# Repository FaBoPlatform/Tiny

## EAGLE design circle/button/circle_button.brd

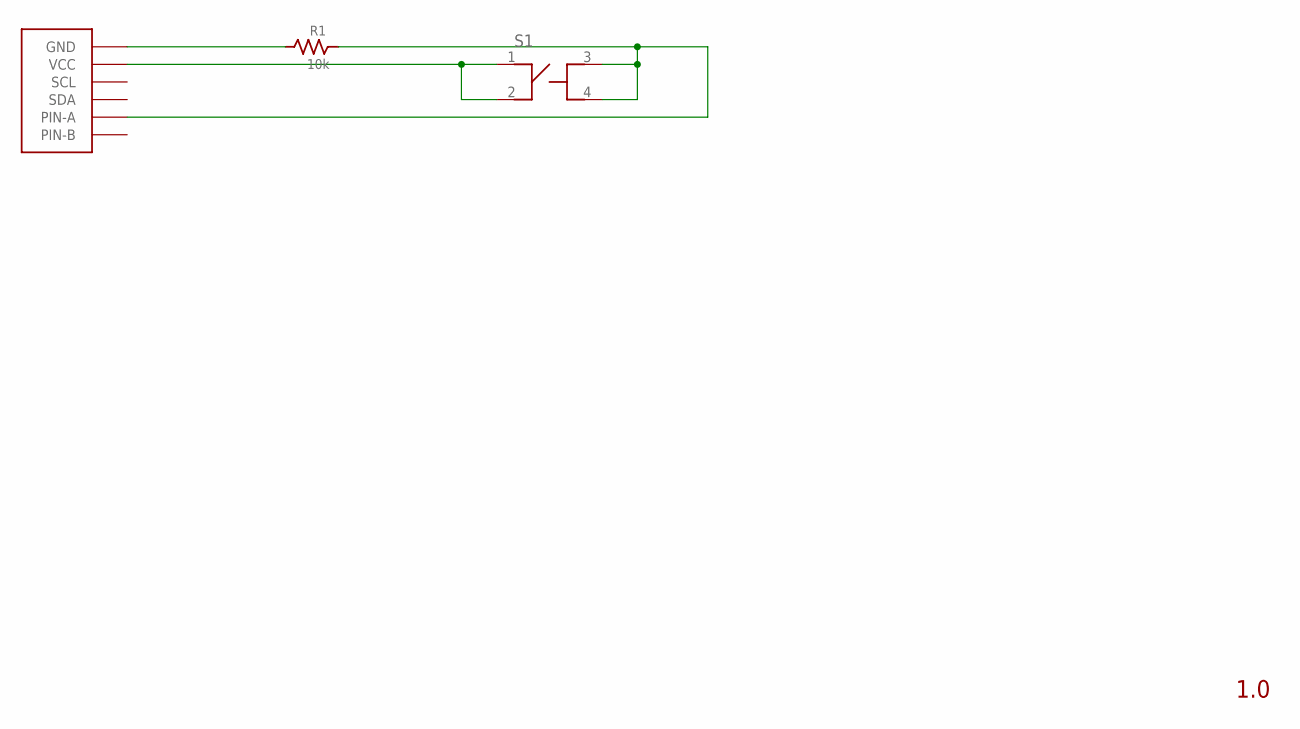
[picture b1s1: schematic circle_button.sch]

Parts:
R1: 10k; 0402
S1: SWITCH-LS6J2M-T
U$2: FABO-NANO

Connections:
GND: R1.P$1 (1), U$2.GND
unnamed: S1.1, S1.2, U$2.VCC
unnamed: R1.P$2 (2), S1.3, S1.4, U$2.2 (PIN-A)

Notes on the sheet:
1.0

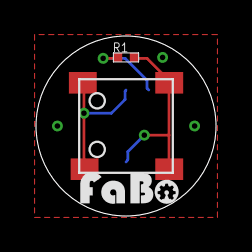
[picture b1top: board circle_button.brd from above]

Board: 2 copper layers, 10.0 x 10.0 mm, 4 parts (0 on the bottom side), 3 nets.

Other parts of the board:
U$1: LOGO_FABO_S

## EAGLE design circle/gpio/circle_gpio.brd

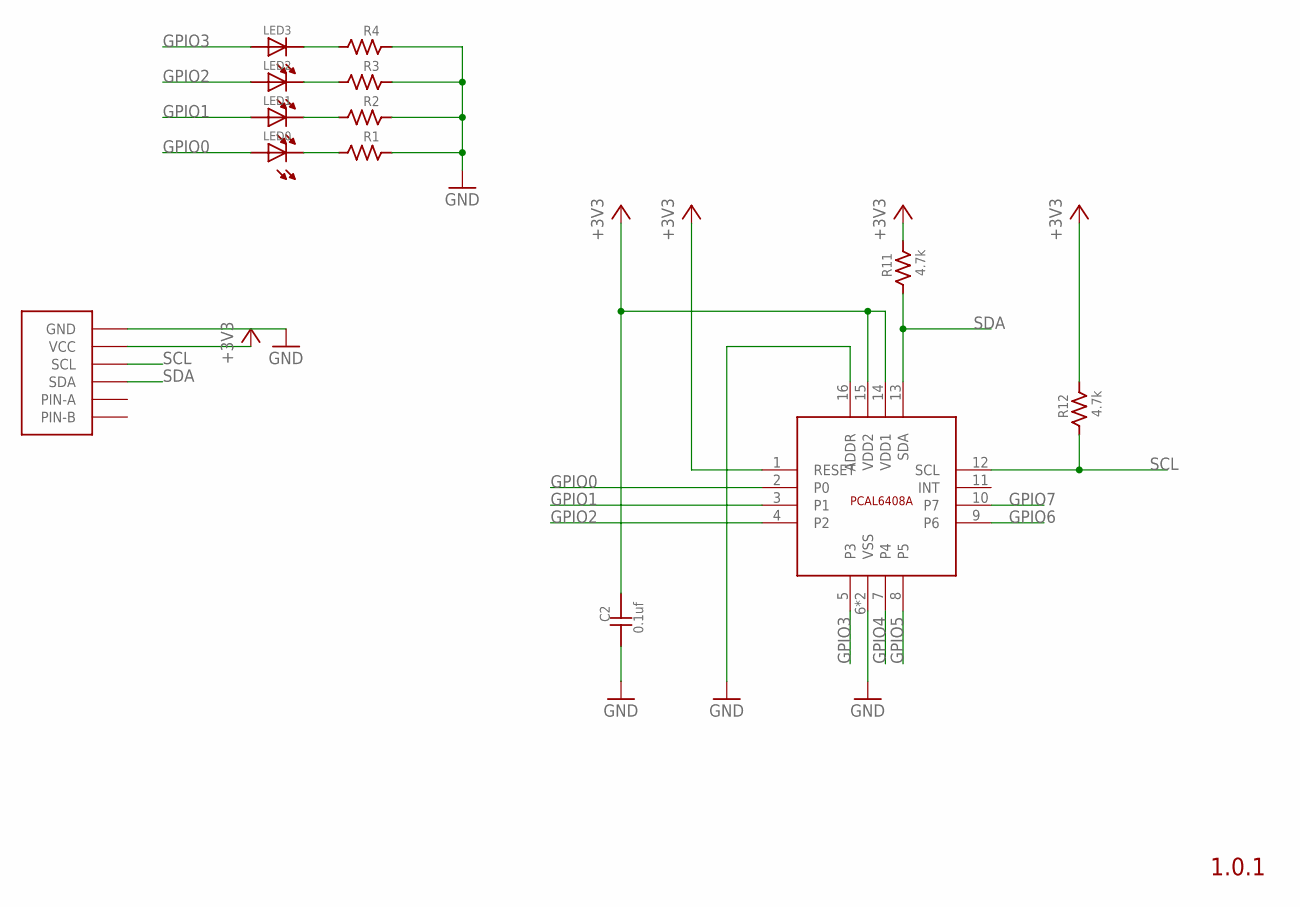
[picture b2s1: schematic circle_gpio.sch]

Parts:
C2: 0.1uf; 0402
LED0, LED1, LED2, LED3: LED0402; 0402
R1, R2, R3, R4: RESISTOR-0402; 0402
R11, R12: 4.7k; 0402
U$3: FABO-NANO
U$5: NX-PCAL6408A; NXP-PCAL6408A

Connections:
111: C2.P$1 (1), R1.P$2 (2), R2.P$2 (2), R3.P$2 (2), R4.P$2 (2), U$3.GND, U$5.6 (VSS), U$5.16 (ADDR), U$5.17 (VSS)
+3V3: C2.P$2 (2), R11.P$2 (2), R12.P$2 (2), U$3.VCC, U$5.1 (RESET), U$5.14 (VDD1), U$5.15 (VDD2)
GPIO0: LED0.ANODE, U$5.2 (P0)
GPIO1: LED1.ANODE, U$5.3 (P1)
GPIO2: LED2.ANODE, U$5.4 (P2)
GPIO3: LED3.ANODE, U$5.5 (P3)
GPIO4: U$5.7 (P4)
GPIO5: U$5.8 (P5)
GPIO6: U$5.9 (P6)
GPIO7: U$5.10 (P7)
unnamed: LED3.CATHODE, R4.P$1 (1)
unnamed: LED2.CATHODE, R3.P$1 (1)
unnamed: LED1.CATHODE, R2.P$1 (1)
unnamed: LED0.CATHODE, R1.P$1 (1)
SCL: R12.P$1 (1), U$3.0 (SCL), U$5.12 (SCL)
SDA: R11.P$1 (1), U$3.1 (SDA), U$5.13 (SDA)

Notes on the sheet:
1.0.1

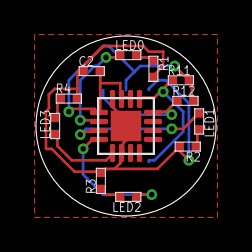
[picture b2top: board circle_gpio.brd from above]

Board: 2 copper layers, 10.0 x 10.0 mm, 13 parts (0 on the bottom side), 12 nets.

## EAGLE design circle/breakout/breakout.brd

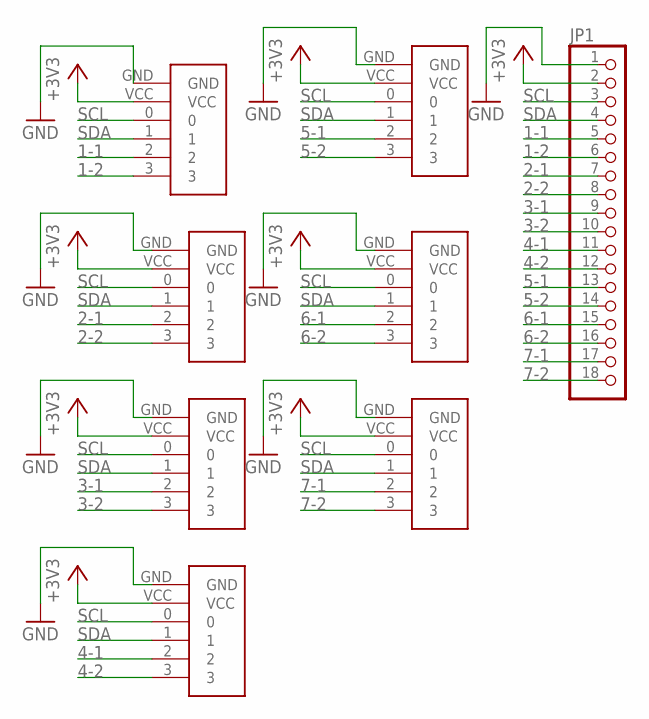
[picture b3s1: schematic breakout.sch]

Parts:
1, 2, 3, 4, 5, 6, 7: FABO-PIN-HEADER-2X3-SMD
JP1: PINHD-1X18; 1X18

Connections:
1-1: 1.2, JP1.5
1-2: 1.3, JP1.6
2-1: 2.2, JP1.7
2-2: 2.3, JP1.8
3-1: 3.2, JP1.9
3-2: 3.3, JP1.10
4-1: 4.2, JP1.11
4-2: 4.3, JP1.12
5-1: 5.2, JP1.13
5-2: 5.3, JP1.14
6-1: 6.2, JP1.15
6-2: 6.3, JP1.16
7-1: 7.2, JP1.17
7-2: 7.3, JP1.18
+3V3: 1.VCC, 2.VCC, 3.VCC, 4.VCC, 5.VCC, 6.VCC, 7.VCC, JP1.2
GND: 1.GND, 2.GND, 3.GND, 4.GND, 5.GND, 6.GND, 7.GND, JP1.1
SCL: 1.0, 2.0, 3.0, 4.0, 5.0, 6.0, 7.0, JP1.3
SDA: 1.1, 2.1, 3.1, 4.1, 5.1, 6.1, 7.1, JP1.4

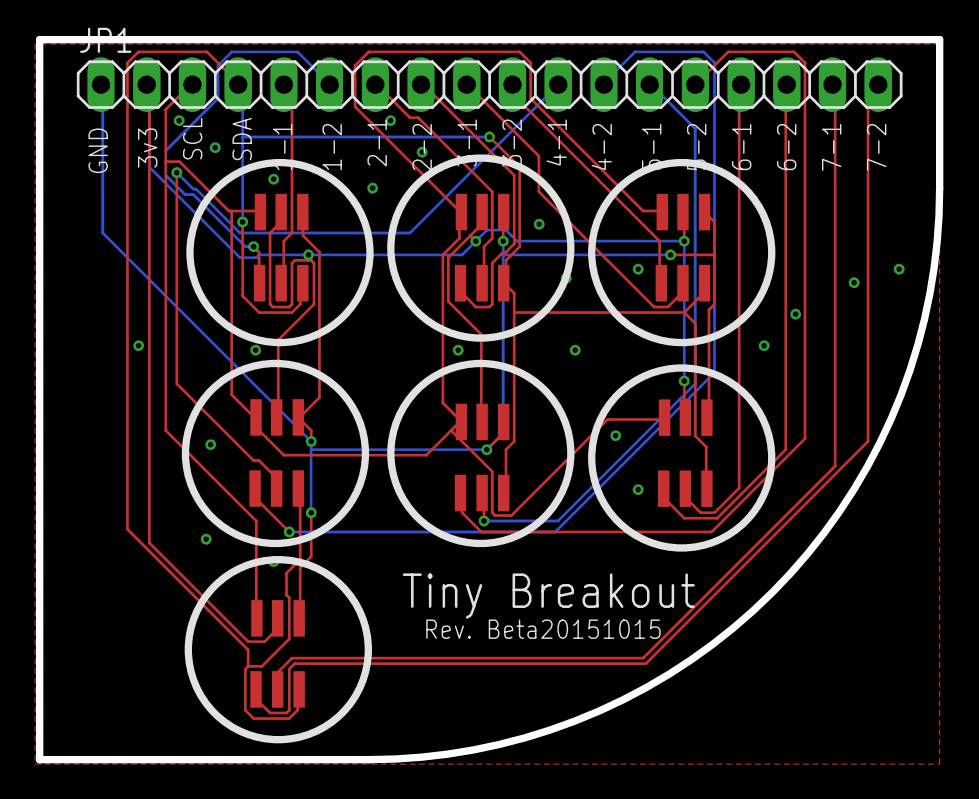
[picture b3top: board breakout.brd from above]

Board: 2 copper layers, 50.0 x 40.0 mm, 8 parts (0 on the bottom side), 18 nets.

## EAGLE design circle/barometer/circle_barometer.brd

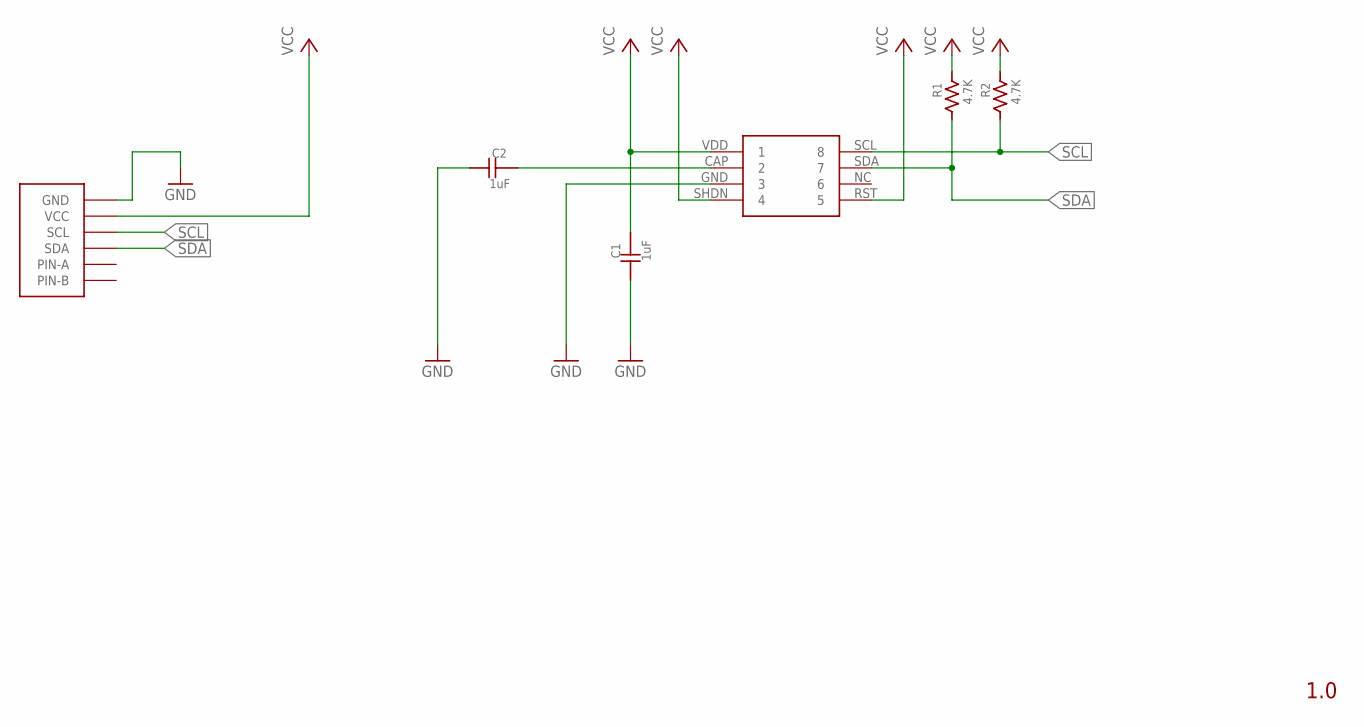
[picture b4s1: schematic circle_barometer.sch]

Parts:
C1, C2: 1uF; 0402
R1, R2: 4.7K; 0402
U$2: I2C-MPL115A2; I2C-MLP115A2
U$4: FABO-NANO

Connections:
GND: C1.P$1 (1), C2.P$1 (1), U$2.GND (3), U$4.GND
unnamed: C2.P$2 (2), U$2.CAP (2)
SCL: R2.P$1 (1), U$2.SCL (8), U$4.0 (SCL)
SDA: R1.P$1 (1), U$2.SDA (7), U$4.1 (SDA)
VCC: C1.P$2 (2), R1.P$2 (2), R2.P$2 (2), U$2.RST (5), U$2.SHDN (4), U$2.VDD (1)

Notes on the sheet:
1.0

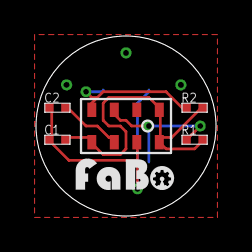
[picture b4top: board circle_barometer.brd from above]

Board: 2 copper layers, 10.0 x 10.0 mm, 7 parts (0 on the bottom side), 5 nets.

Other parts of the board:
U$3: LOGO_FABO_S

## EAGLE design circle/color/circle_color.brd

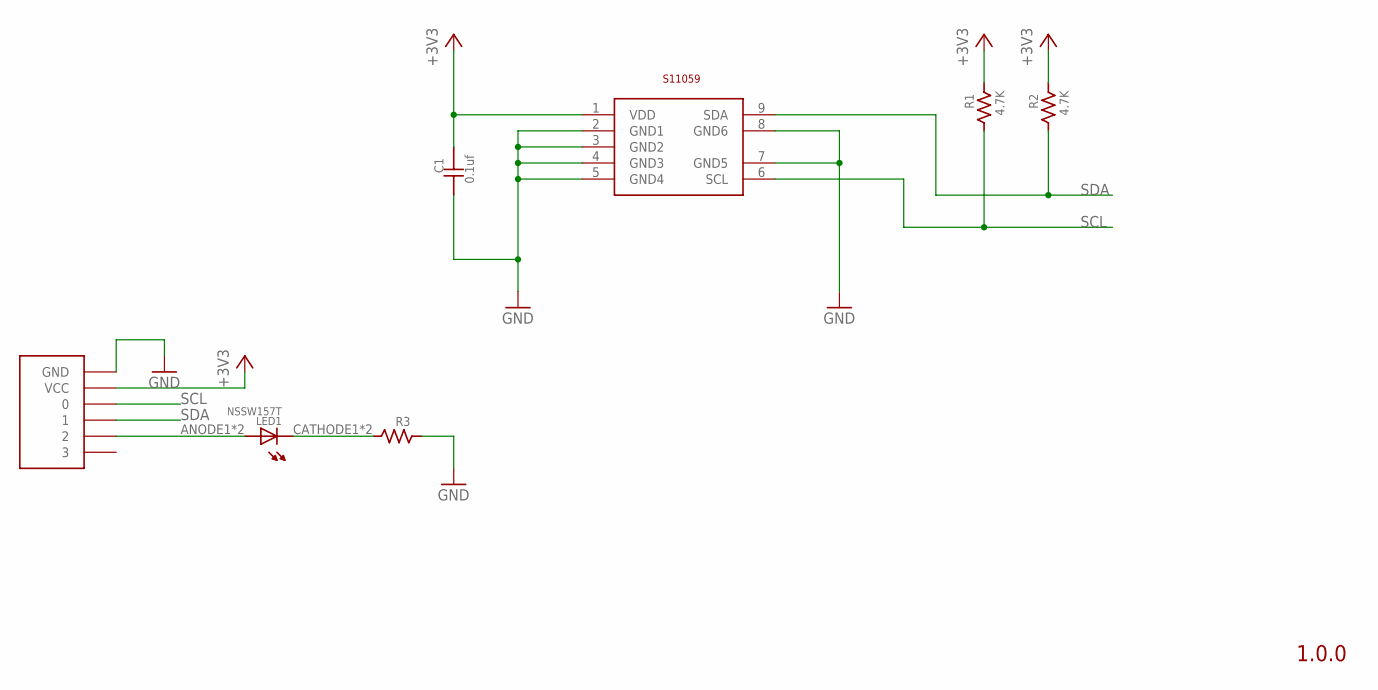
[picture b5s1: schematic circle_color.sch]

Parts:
C1: 0.1uf; 0402
LED1: NSSW157T
R1, R2: 4.7K; 0402
R3: RESISTOR-0402; 0402
S1: HAMAMATSU-S11059
U$4: FABO-NANO

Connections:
+3V3: C1.P$2 (2), R1.P$2 (2), R2.P$2 (2), S1.1 (VDD), U$4.VCC
GND: C1.P$1 (1), R3.P$2 (2), S1.2 (GND1), S1.3 (GND2), S1.4 (GND3), S1.5 (GND4), S1.7 (GND5), S1.8 (GND6), U$4.GND
unnamed: LED1.ANODE1 (ANODE), LED1.ANODE2 (ANODE), U$4.2
unnamed: LED1.CATHODE1 (CATHODE), LED1.CATHODE2 (CATHODE), R3.P$1 (1)
SCL: R1.P$1 (1), S1.6 (SCL), U$4.0
SDA: R2.P$1 (1), S1.9 (SDA), U$4.1

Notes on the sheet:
1.0.0

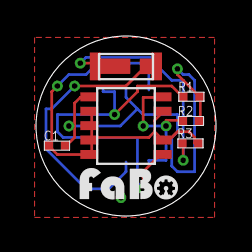
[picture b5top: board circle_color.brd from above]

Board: 2 copper layers, 10.0 x 10.0 mm, 8 parts (0 on the bottom side), 6 nets.

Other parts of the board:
U$2: LOGO_FABO_S

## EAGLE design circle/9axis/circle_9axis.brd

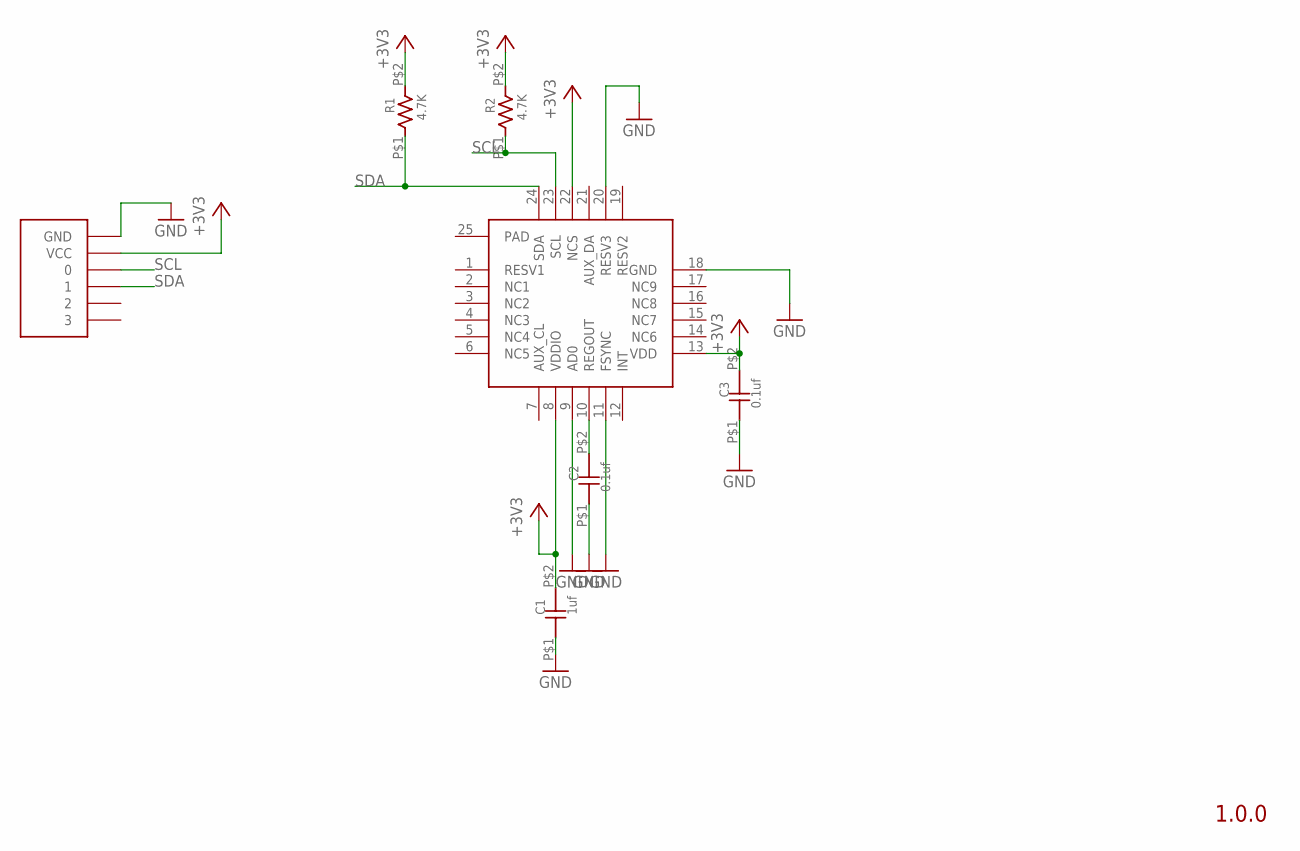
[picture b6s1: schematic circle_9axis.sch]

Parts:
C1: 1uf; 0402
C2, C3: 0.1uf; 0402
R1, R2: 4.7K; 0402
U$1: INVENSENSE-MPU9250; LGA-24
U$4: FABO-NANO

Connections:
+3V3: C1.P$2 (2), C3.P$2 (2), R1.P$2 (2), R2.P$2 (2), U$1.8 (VDDIO), U$1.13 (VDD), U$1.22 (NCS), U$4.VCC
GND: C1.P$1 (1), C2.P$1 (1), C3.P$1 (1), U$1.9 (AD0), U$1.11 (FSYNC), U$1.18 (GND), U$1.20 (RESV3), U$4.GND
unnamed: C2.P$2 (2), U$1.10 (REGOUT)
SCL: R2.P$1 (1), U$1.23 (SCL), U$4.0
SDA: R1.P$1 (1), U$1.24 (SDA), U$4.1

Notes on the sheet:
1.0.0

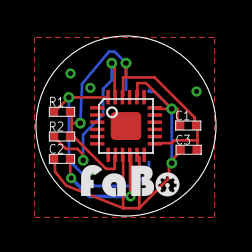
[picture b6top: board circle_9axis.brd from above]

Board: 2 copper layers, 10.0 x 10.0 mm, 8 parts (0 on the bottom side), 5 nets.

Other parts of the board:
U$3: LOGO_FABO_S

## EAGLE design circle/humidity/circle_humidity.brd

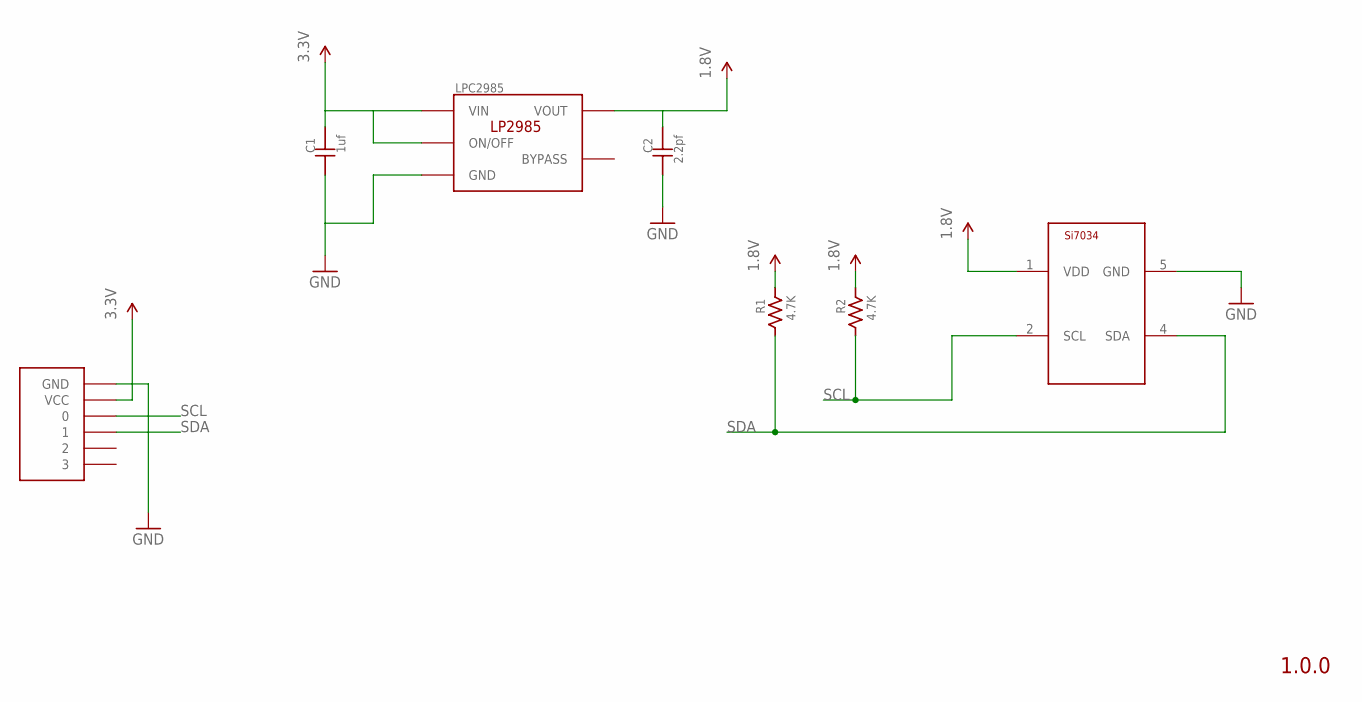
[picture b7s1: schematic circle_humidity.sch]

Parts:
C1: 1uf; 0402
C2: 2.2pf; 0402
LPC2985: TI-LP2985-18DBVT; TI-LP2985
R1, R2: 4.7K; 0402
U$5: FABO-NANO
U$6: SILICONLABS-SI7034

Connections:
1.8V: C2.P$2 (2), LPC2985.5 (VOUT), R1.P$2 (2), R2.P$2 (2), U$6.1 (VDD)
3.3V: C1.P$2 (2), LPC2985.1 (VIN), LPC2985.3 (ON/OFF), U$5.VCC
GND: C1.P$1 (1), C2.P$1 (1), LPC2985.2 (GND), U$5.GND, U$6.5 (GND)
SCL: R2.P$1 (1), U$5.0, U$6.2 (SCL)
SDA: R1.P$1 (1), U$5.1, U$6.4 (SDA)

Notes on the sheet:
1.0.0

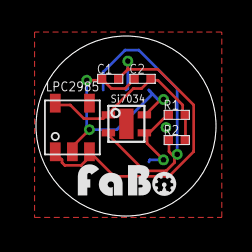
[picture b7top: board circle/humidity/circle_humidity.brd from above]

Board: 2 copper layers, 10.0 x 10.0 mm, 8 parts (0 on the bottom side), 5 nets.

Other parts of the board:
U$2: LOGO_FABO_S

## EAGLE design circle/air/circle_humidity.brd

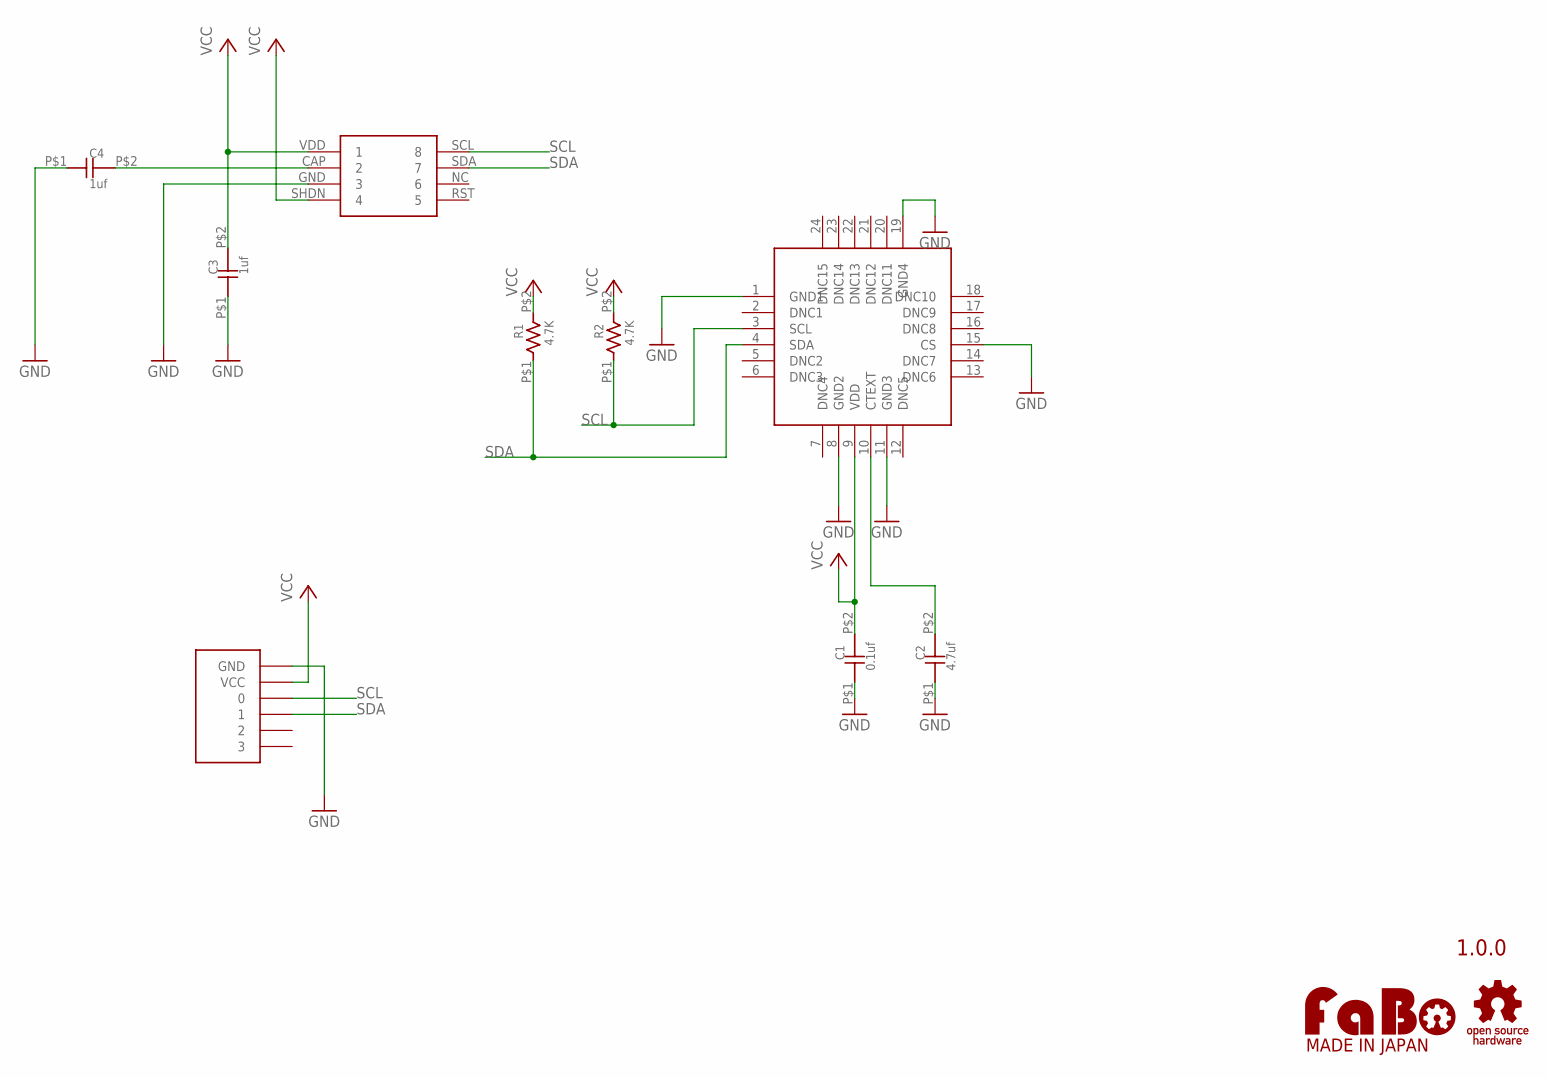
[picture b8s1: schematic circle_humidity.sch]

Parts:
C1: 0.1uf; 0402
C2: 4.7uf; 0402
C3, C4: 1uf; 0402
R1, R2: 4.7K; 0402
SI1: SILICONLAB-SI7005
U$2: LOGO_OSHW-S_BOTTOM; LOGO_OSHW_S_BOTTOM
U$3: I2C-MPL115A2; I2C-MLP115A2
U$4: LOGO_FABO-S_BOTTOM; LOGO_FABO_S_BOTTOM
U$5: FABO-NANO

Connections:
GND: C1.P$1 (1), C2.P$1 (1), C3.P$1 (1), C4.P$1 (1), SI1.1 (GND1), SI1.8 (GND2), SI1.11 (GND3), SI1.15 (CS), SI1.19 (GND4), U$3.GND (3), U$5.GND
unnamed: C2.P$2 (2), SI1.10 (CTEXT)
unnamed: C4.P$2 (2), U$3.CAP (2)
SCL: R2.P$1 (1), SI1.3 (SCL), U$3.SCL (8), U$5.0
SDA: R1.P$1 (1), SI1.4 (SDA), U$3.SDA (7), U$5.1
VCC: C1.P$2 (2), C3.P$2 (2), R1.P$2 (2), R2.P$2 (2), SI1.9 (VDD), U$3.SHDN (4), U$3.VDD (1), U$5.VCC

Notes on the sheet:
1.0.0

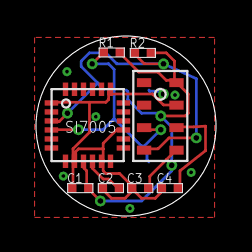
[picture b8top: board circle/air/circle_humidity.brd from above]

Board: 2 copper layers, 10.0 x 10.0 mm, 11 parts (0 on the bottom side), 6 nets.

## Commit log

2015-09-14 Update circle
2015-09-14 Add barometer
2015-10-16 Add breakout board
2015-10-16 Add circle of button
2015-10-16 Update jig

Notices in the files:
parts and their libraries:
gclue: Released under the Creative Commons
gclue: https://creativecommons.org/licenses/by-sa/4.0
FaBo-etc: Released under the Creative Commons Attribution-ShareAlike 4.0 License
